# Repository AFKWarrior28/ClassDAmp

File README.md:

# ClassDAmp
Class-D Amplifier soldering and electronics exercise at the University of Waterloo, Department of Physics and Astronomy. Kits are available for free to members of the University of Waterloo community, including staff and faculty. All we ask for is a willingness to learn and explore the amazing world of electronics!

A class-D amplifier is a type of audio amplifier that works by turning an analog (continuous) audio signal into a digital (either on or off) signal, amplifying it, then converting it back into an analog signal for speakers to play. Essentially, it's what allows computers and phones to power large speakers. In this project, you will learn the basics of soldering and electronic components while building your very own amplifier-speaker combo!

The kit includes: 1x Class-D amplifier PCB, 1x component bag, and 1x speaker driver. In order to recieve a kit, you must complete the Science Resource Shop Orientation course (self-register on LEARN). Once that is complete, please email me at j6hao@uwaterloo.ca to arrange for a kit pickup.  

# Science Resource Shop
The [Science Resource Shop](https://uwaterloo.ca/science-technical-services/about-science-technical-services/science-resource-shop) is located in the room PHY135. Besides soldering, they offer a wide array of tools and machines such as lathes, mills, bandsaws, and 3D printers. I highly recommend exploring the various tools offered to create a unique housing for your speaker and PCB. A sample 3D design is included in this repository, and I encourage you to improve upon my design.

On Fridays from 1pm to 3pm, I am available for soldering help in the Science Resource Shop. Please E-Mail me 24 hours in advance if you require any help with putting together your kit!

# Instructional Videos

[Here](https://youtube.com/playlist?list=PLA1I_6hQhSNaFf6GUz-gZa_wceobiq_6l&si=VTzpREcftJKnDZTa) is a playlist of instructional videos that I am making for this project. There is important info in the description of each video, so please watch them as needed and read carefully! It's my first time making videos like this, so please excuse the production value :3 

UPDATE: All soldering videos are now available through the Youtube link. Some additional material like testing instructions are still in production.

# PCB Design
All PCB design is conducted using the free software [KiCAD](https://www.kicad.org). All final design files for the PCB are included in this repository, and I encourage you to explore them and improve upon my design.

# Speaker Housing
The speaker boxes are designed to share the same back. The back can be mounted on the box using magnets, but the tolerances allow for a good friction fit. Included in the design are sockets for 4x 8-32 heat-set inserts for mounting the speaker and 3x 4-40 or M3 set screws for mounting the PCB. The 3 mounting holes on the PCB are sized for M3 but are also compatable with 4-40 fittings.

The PCB's mounting holes are placed as follows, relative to the bottom left corner of the PCB: (5, 50)mm, (170, 95)mm, (170, 10)mm.

# Custom Development Area
The custom development area included on the ClassDAmp PCB is an area for you to explore and create. Before soldering components to the PCB, it is recommended that you test your circuit on a breadboard. After building on the custom development area, use an external power supply (not USB-C!) to check the functionality of your circuit to prevent any damage to your power supply in the event of a short circuit.  

The USB-C power supply is designed to be able to provide 5VDC with a maximum current draw of 3A. Always check the specification of your power supply and make sure it can supply the necessary current. If your circuit requires more power you will have to create your own power supply.

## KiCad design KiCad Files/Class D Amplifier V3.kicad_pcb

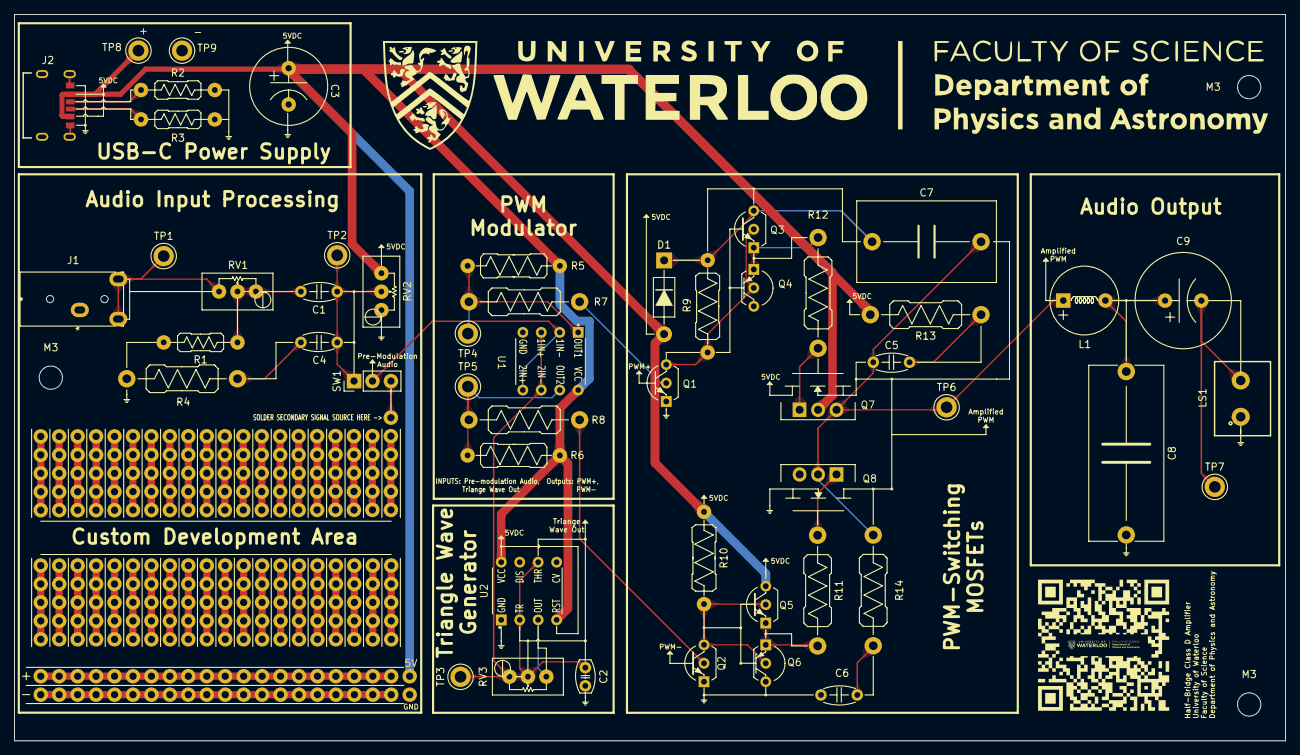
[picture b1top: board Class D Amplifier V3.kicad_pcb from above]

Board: 2 copper layers, 175.0 x 100.0 mm, 55 parts (0 on the bottom side), 27 nets.

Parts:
C1, C4, C5, C6: 100n; C_Disc_D5.0mm_W2.5mm_P5.00mm
C2: 10n; C_Disc_D5.0mm_W2.5mm_P2.50mm
C3: 1m; CAP_PK&slash_PZ_10X20_LOW_RUB
C7: 2.2u; C_Rect_L19.0mm_W11.0mm_P15.00mm_MKS4
C8: 3u; C_Rect_L24.0mm_W10.1mm_P22.50mm_MKT
C9: 3300u; CAP_PK&slash_PZ_12P5X20_LOW_RUB
Custom Development Area: Breadboard
D1: 1N5819; D_DO-41_SOD81_P10.16mm_Horizontal
J1: STX-3000; STX-3000_KYC
J2: USB_C_Receptacle_PowerOnly_24P; GCT_USB4125-GF-A_REVA2
L1: 22u; IND_BOURNS_RLB0912
LS1: 40Ω; 691137710002
M3, M3#2, M3#3: MountingHole_3.2mm_M3
Q1, Q2, Q3, Q5: 2N4401; NPN_Schematic
Q4, Q6: 2N2907A; PNP_Schematic
Q7, Q8: IRLZ14PBF; NMOS Schematic
R1: 10k; R_Axial_DIN0207_L6.3mm_D2.5mm_P10.16mm_Horizontal
R2, R3: 5.1k; R_Axial_DIN0207_L6.3mm_D2.5mm_P10.16mm_Horizontal
R4, R7, R8, R11, R12, R13, R14: 10; R_Axial_DIN0411_L9.9mm_D3.6mm_P15.24mm_Horizontal
R5, R6, R9, R10: 1k; R_Axial_DIN0309_L9.0mm_D3.2mm_P12.70mm_Horizontal
RV1: 5k; Potentiometer_Bourns_3296W_Vertical
RV2: 20k; Potentiometer_Bourns_3296W_Vertical
RV3: 2k; Potentiometer_Bourns_3296W_Vertical
SW1: SW_SPDT; PinHeader_1x03_P2.54mm_Vertical
TP1, TP2, TP3, TP4, TP5, TP6, TP7, TP8, TP9: TestPoint; TestPoint_Keystone_5010-5014_Multipurpose
U1: LM393
U2: NE555P; TLC555CP

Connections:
+5V: C3.1, D1.2 (A), J2.A9 (VBUS), J2.B9 (VBUS), Q5.3 (C), Q7.2 (D), R5.1, R6.1, R10.1, R13.2, RV2.3, TP8.1, U1.8 (Vcc), U2.4 (R), U2.8 (VCC)
GND: C2.2, C3.2, C6.2, C8.2, J1.1, J2.A12 (GND), J2.B12 (GND), J2.S1 (SHIELD), LS1.1, Q1.1 (E), Q2.1 (E), Q4.3 (C), Q6.3 (C), Q8.3 (S), R1.2, R2.2, R3.2, R4.1, RV2.1, TP9.1, U1.4 (Gnd), U2.1 (GND)
unnamed: C1.2, R1.1, RV1.1, RV1.2
unnamed: C4.1, R4.2
unnamed: C5.1, R13.1
unnamed: C6.1, R14.1
unnamed: C8.1, C9.1, L1.2
unnamed: C9.2, LS1.2, TP7.1
unnamed: C7.1, D1.1 (K), Q3.3 (C), R9.1
unnamed: J1.2, J1.3, RV1.3, TP1.1
unnamed: J2.A5 (CC1), R2.1
unnamed: J2.B5 (CC2), R3.1
unnamed: Q1.2 (B), R7.1
unnamed: Q1.3 (C), Q3.2 (B), Q4.2 (B), R9.2
unnamed: Q2.2 (B), R8.1
unnamed: Q2.3 (C), Q5.2 (B), Q6.2 (B), R10.2
unnamed: Q3.1 (E), Q4.1 (E), R12.2
unnamed: Q5.1 (E), Q6.1 (E), R11.2
unnamed: Q7.1 (G), R12.1
unnamed: C5.2, C7.2, L1.1, Q7.3 (S), Q8.2 (D), R14.2, TP6.1
unnamed: Q8.1 (G), R11.1
unnamed: C1.1, C4.2, RV2.2, SW1.1 (A), TP2.1
unnamed: SW1.2 (B), U1.2 (1IN-), U1.5 (2IN+)
unnamed: C2.1, RV3.1, RV3.2, TP3.1, U1.3 (1IN+), U1.6 (2IN-), U2.2 (TR), U2.6 (THR)
unnamed: R5.2, R7.2, TP4.1, U1.1 (OUT1)
unnamed: R6.2, R8.2, TP5.1, U1.7 (OUT2)
unnamed: RV3.3, U2.3 (Q)

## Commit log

2025-12-02 PCB v2
2025-12-02 Create LICENSE
2025-12-19 Final Design FIles
2026-02-20 Add .gitignore for KiCad and temporary files
